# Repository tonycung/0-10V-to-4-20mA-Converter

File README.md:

# 0-10V-to-4-20mA-Converter
A simple 0–10 V to 4–20 mA analog signal converter designed with KiCad.

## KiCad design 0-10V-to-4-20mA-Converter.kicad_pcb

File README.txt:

# 0–10 V to 4–20 mA Converter

A simple analog voltage-to-current converter designed with KiCad.

## Project Objective

Design a PCB that converts a 0–10 V input signal into a proportional 4–20 mA output.

## Target

| Vin | Iout |
|---:|---:|
| 0 V | 4 mA |
| 2.5 V | 8 mA |
| 5 V | 12 mA |
| 7.5 V | 16 mA |
| 10 V | 20 mA |

## Tools

- KiCad
- LTspice
- Git / GitHub

## Status

Project initialization.

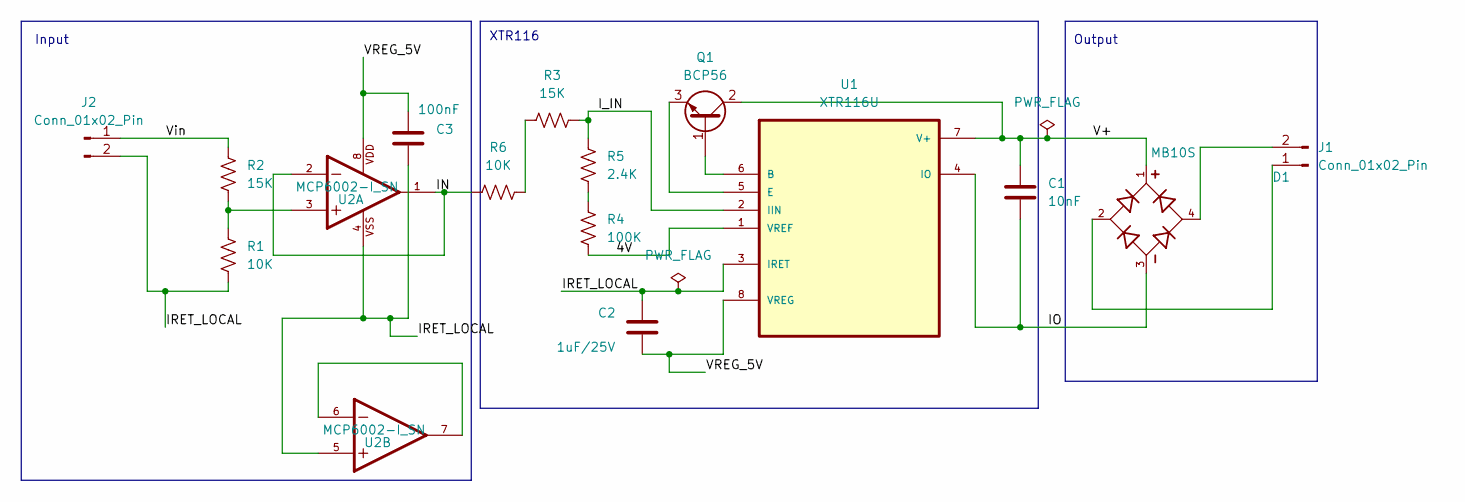
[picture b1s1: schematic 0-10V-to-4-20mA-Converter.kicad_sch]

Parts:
C1: 10nF; C_0805_2012Metric_Pad1.18x1.45mm_HandSolder
C2: 1uF/25V; C_0805_2012Metric_Pad1.18x1.45mm_HandSolder
C3: 100nF; C_0805_2012Metric_Pad1.18x1.45mm_HandSolder
D1: MB10S; MB10S_DiodesInc
J1, J2: Conn_01x02_Pin; KF301-2P_Universal_P5.08
Q1: BCP56; SOT-223-3_TabPin2
R1, R6: 10K; R_0805_2012Metric_Pad1.20x1.40mm_HandSolder
R2, R3: 15K; R_0805_2012Metric_Pad1.20x1.40mm_HandSolder
R4: 100K; R_0805_2012Metric_Pad1.20x1.40mm_HandSolder
R5: 2.4K; R_0805_2012Metric_Pad1.20x1.40mm_HandSolder
U1: XTR116U; SOIC-8_3.9x4.9mm_P1.27mm
U2: MCP6002-I_SN; SOIC-8_3.9x4.9mm_P1.27mm; PARTREV L

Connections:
/4V: R4.2, U1.1 (VREF)
/IN: R6.1, U2.1, U2.2
/IO: C1.2, D1.3, U1.4 (IO)
/IRET_LOCAL: C2.1, C3.2, J2.2, R1.2, U1.3 (IRET), U2.4, U2.5
/I_IN: R3.2, R5.1, U1.2 (IIN)
/V+: C1.1, D1.1, Q1.2 (C), U1.7 (V+)
/VREG_5V: C2.2, C3.1, U1.8 (VREG), U2.8
/Vin: J2.1, R2.1
unnamed: D1.2, J1.1
unnamed: D1.4, J1.2
unnamed: Q1.1 (B), U1.6 (B)
unnamed: Q1.3 (E), U1.5 (E)
unnamed: R1.1, R2.2, U2.3
unnamed: R3.1, R6.2
unnamed: R4.1, R5.2
unnamed: U2.6, U2.7

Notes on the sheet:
XTR116
Output
Input

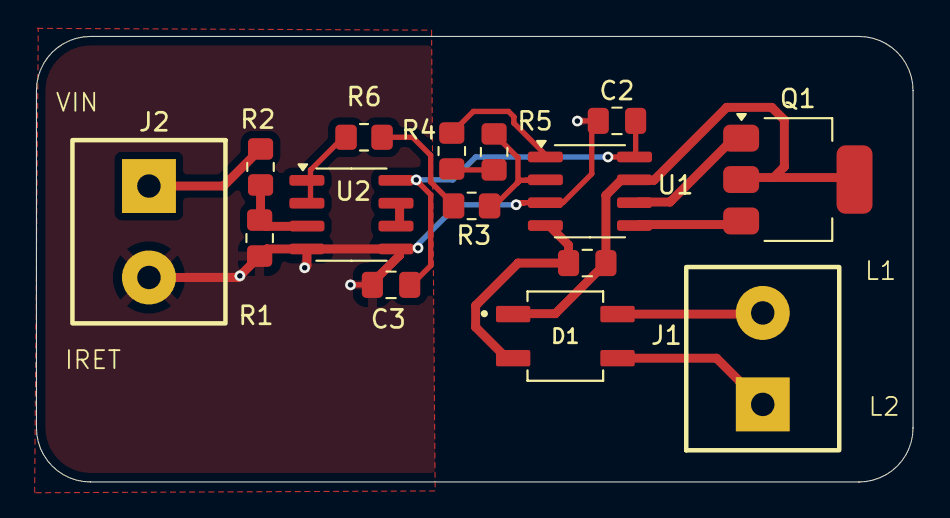
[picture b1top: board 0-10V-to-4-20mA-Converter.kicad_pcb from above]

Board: 2 copper layers, 48.7 x 24.8 mm, 15 parts (0 on the bottom side), 16 nets.
